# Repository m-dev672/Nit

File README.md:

# Nit
Palm-sized non intelligent terminal (= Dumb Terminal) made with Arduino.

Currently under development. Not available.

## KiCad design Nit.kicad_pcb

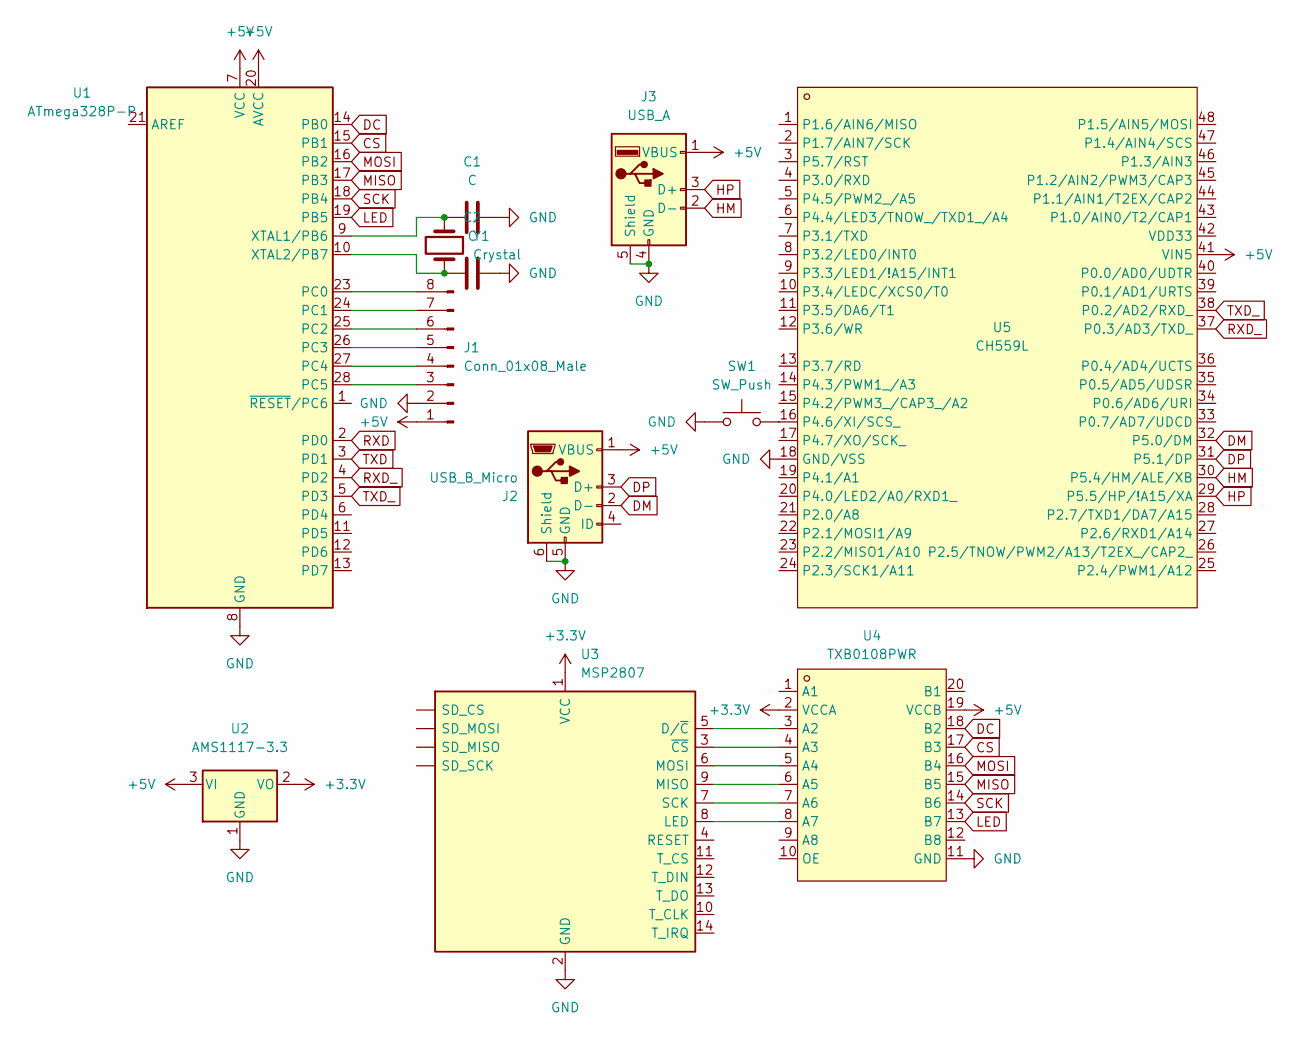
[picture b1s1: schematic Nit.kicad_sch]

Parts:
C1, C2: C; C_0603_1608Metric
J1: Conn_01x08_Male
J2: USB_B_Micro; USB_Micro-B_C2682230
J3: USB_A; USB_Type-A_C2345
SW1: SW_Push; Push_SW_C2693625
U1: ATmega328P-P; DIP-28_W7.62mm
U2: AMS1117-3.3; SOT-223-3_TabPin2
U3: MSP2807; PinHeader_1x14_P2.54mm_Vertical
U4: TXB0108PWR; TSSOP-20_4.4x6.5mm_P0.65mm; LCSC Part C53406
U5: CH559L; LQFP-48_7x7mm_P0.5mm; LCSC Part C150548
Y1: Crystal; Crystal_C16212

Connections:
+3.3V: U2.2 (VO), U3.1 (VCC), U4.2 (VCCA)
+5V: J1.1, J2.1 (VBUS), J3.1 (VBUS), U1.7 (VCC), U1.20 (AVCC), U2.3 (VI), U4.19 (VCCB), U5.41 (VIN5)
CS: U1.15 (PB1), U4.17 (B3)
DC: U1.14 (PB0), U4.18 (B2)
DM: J2.2 (D-), U5.32 (P5.0/DM)
DP: J2.3 (D+), U5.31 (P5.1/DP)
GND: C1.2, C2.2, J1.2, J2.5 (GND), J2.6 (Shield), J3.4 (GND), J3.5 (Shield), SW1.1, U1.8 (GND), U1.22 (GND), U2.1 (GND), U3.2 (GND), U4.11 (GND), U5.18 (GND/VSS)
HM: J3.2 (D-), U5.30 (P5.4/HM/ALE/XB)
HP: J3.3 (D+), U5.29 (P5.5/HP/!A15/XA)
LED: U1.19 (PB5), U4.13 (B7)
MISO: U1.17 (PB3), U4.15 (B5)
MOSI: U1.16 (PB2), U4.16 (B4)
unnamed: C1.1, U1.9 (XTAL1/PB6), Y1.1
unnamed: C2.1, U1.10 (XTAL2/PB7), Y1.2
unnamed: J1.3, U1.28 (PC5)
unnamed: J1.4, U1.27 (PC4)
unnamed: J1.5, U1.26 (PC3)
unnamed: J1.6, U1.25 (PC2)
unnamed: J1.7, U1.24 (PC1)
unnamed: J1.8, U1.23 (PC0)
unnamed: SW1.2, U5.16 (P4.6/XI/SCS_)
unnamed: U3.3 (~CS), U4.4 (A3)
unnamed: U3.5 (D/~C), U4.3 (A2)
unnamed: U3.6 (MOSI), U4.5 (A4)
unnamed: U3.7 (SCK), U4.7 (A6)
unnamed: U3.8 (LED), U4.8 (A7)
unnamed: U3.9 (MISO), U4.6 (A5)
RXD: U1.2 (PD0)
RXD_: U1.4 (PD2), U5.37 (P0.3/AD3/TXD_)
SCK: U1.18 (PB4), U4.14 (B6)
TXD: U1.3 (PD1)
TXD_: U1.5 (PD3), U5.38 (P0.2/AD2/RXD_)

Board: 2 copper layers, 12 parts (0 on the bottom side), 30 nets, no tracks yet.

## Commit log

2022-08-14 second commit
2022-08-14 completed schematic
2022-08-14 Update MSP2807 schematic
